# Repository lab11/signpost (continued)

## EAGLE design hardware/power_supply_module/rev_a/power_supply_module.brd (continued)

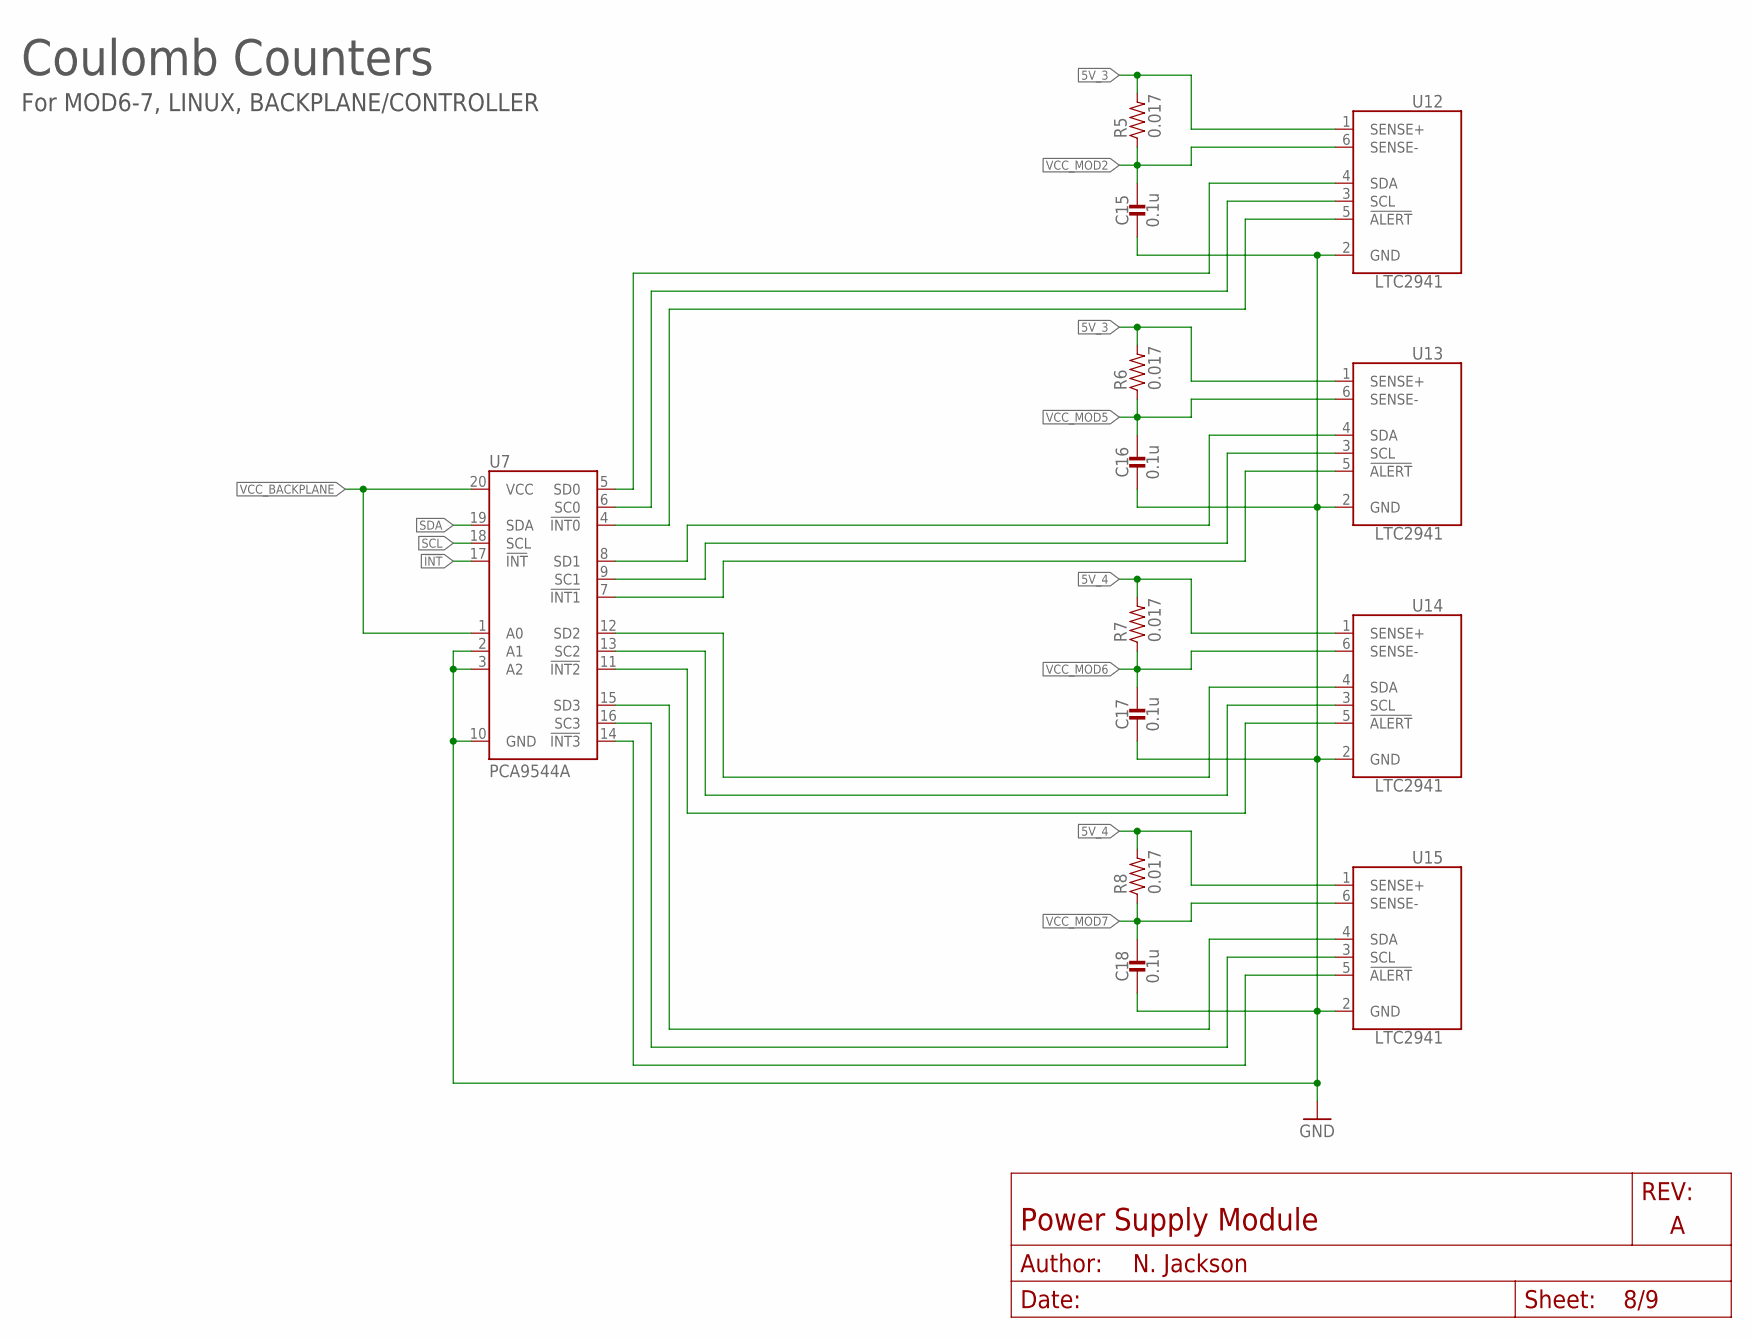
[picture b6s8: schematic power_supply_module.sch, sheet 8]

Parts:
C15, C16, C17, C18: 0.1u; 0402_CAP
R5, R6, R7, R8: 0.017; 0805_RES
U7: PCA9544A; SO20L
U12, U13, U14, U15: LTC2941; DFN-6-2MMX3MM

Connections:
5V_3: R5.2, R6.2, U12.1 (SENSE+), U13.1 (SENSE+); also elsewhere on the board
5V_4: R7.2, R8.2, U14.1 (SENSE+), U15.1 (SENSE+); also elsewhere on the board
!INT: U7.17 (!INT); also elsewhere on the board
GND: C15.2, C16.2, C17.2, C18.2, U7.2 (A1), U7.3 (A2), U7.10 (GND), U12.2 (GND), U13.2 (GND), U14.2 (GND), U15.2 (GND); also elsewhere on the board
unnamed: U7.5 (SD0), U12.4 (SDA)
unnamed: U7.6 (SC0), U12.3 (SCL)
unnamed: U7.12 (SD2), U14.4 (SDA)
unnamed: U7.13 (SC2), U14.3 (SCL)
unnamed: U7.11 (!INT2), U14.5 (!ALERT)
unnamed: U7.15 (SD3), U15.4 (SDA)
unnamed: U7.16 (SC3), U15.3 (SCL)
unnamed: U7.14 (!INT3), U15.5 (!ALERT)
unnamed: U7.4 (!INT0), U12.5 (!ALERT)
unnamed: U7.8 (SD1), U13.4 (SDA)
unnamed: U7.9 (SC1), U13.3 (SCL)
unnamed: U7.7 (!INT1), U13.5 (!ALERT)
SCL: U7.18 (SCL); also elsewhere on the board
SDA: U7.19 (SDA); also elsewhere on the board
VCC_BACKPLANE: U7.1 (A0), U7.20 (VCC); also elsewhere on the board
VCC_MOD2: C15.1, R5.1, U12.6 (SENSE-); also elsewhere on the board
VCC_MOD5: C16.1, R6.1, U13.6 (SENSE-); also elsewhere on the board
VCC_MOD6: C17.1, R7.1, U14.6 (SENSE-); also elsewhere on the board
VCC_MOD7: C18.1, R8.1, U15.6 (SENSE-); also elsewhere on the board

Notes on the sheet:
Coulomb Counters
For MOD6-7, LINUX, BACKPLANE/CONTROLLER

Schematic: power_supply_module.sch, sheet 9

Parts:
TP1, TP2, TP3, TP4, TP5, TP6, TP7, TP8, TP9, TP10, TP11, TP12, TP13, TP14, TP15, TP16, TP17, TP18, TP19, TP20: TEST_POINT_0.040IN; TESTPOINT_0.040IN

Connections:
3V3: TP5.TESTPOINT; also elsewhere on the board
5V_1: TP6.TESTPOINT; also elsewhere on the board
5V_2: TP7.TESTPOINT; also elsewhere on the board
5V_3: TP8.TESTPOINT; also elsewhere on the board
5V_4: TP9.TESTPOINT; also elsewhere on the board
!INT: TP20.TESTPOINT; also elsewhere on the board
GND: TP4.TESTPOINT; also elsewhere on the board
SCL: TP19.TESTPOINT; also elsewhere on the board
SDA: TP18.TESTPOINT; also elsewhere on the board
VBATT: TP3.TESTPOINT; also elsewhere on the board
VCC_BACKPLANE: TP11.TESTPOINT; also elsewhere on the board
VCC_LINUX: TP10.TESTPOINT; also elsewhere on the board
VCC_MOD0: TP12.TESTPOINT; also elsewhere on the board
VCC_MOD1: TP13.TESTPOINT; also elsewhere on the board
VCC_MOD2: TP14.TESTPOINT; also elsewhere on the board
VCC_MOD5: TP15.TESTPOINT; also elsewhere on the board
VCC_MOD6: TP16.TESTPOINT; also elsewhere on the board
VCC_MOD7: TP17.TESTPOINT; also elsewhere on the board
VSOL+: TP1.TESTPOINT; also elsewhere on the board
VSOL-: TP2.TESTPOINT; also elsewhere on the board

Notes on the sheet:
Debugging

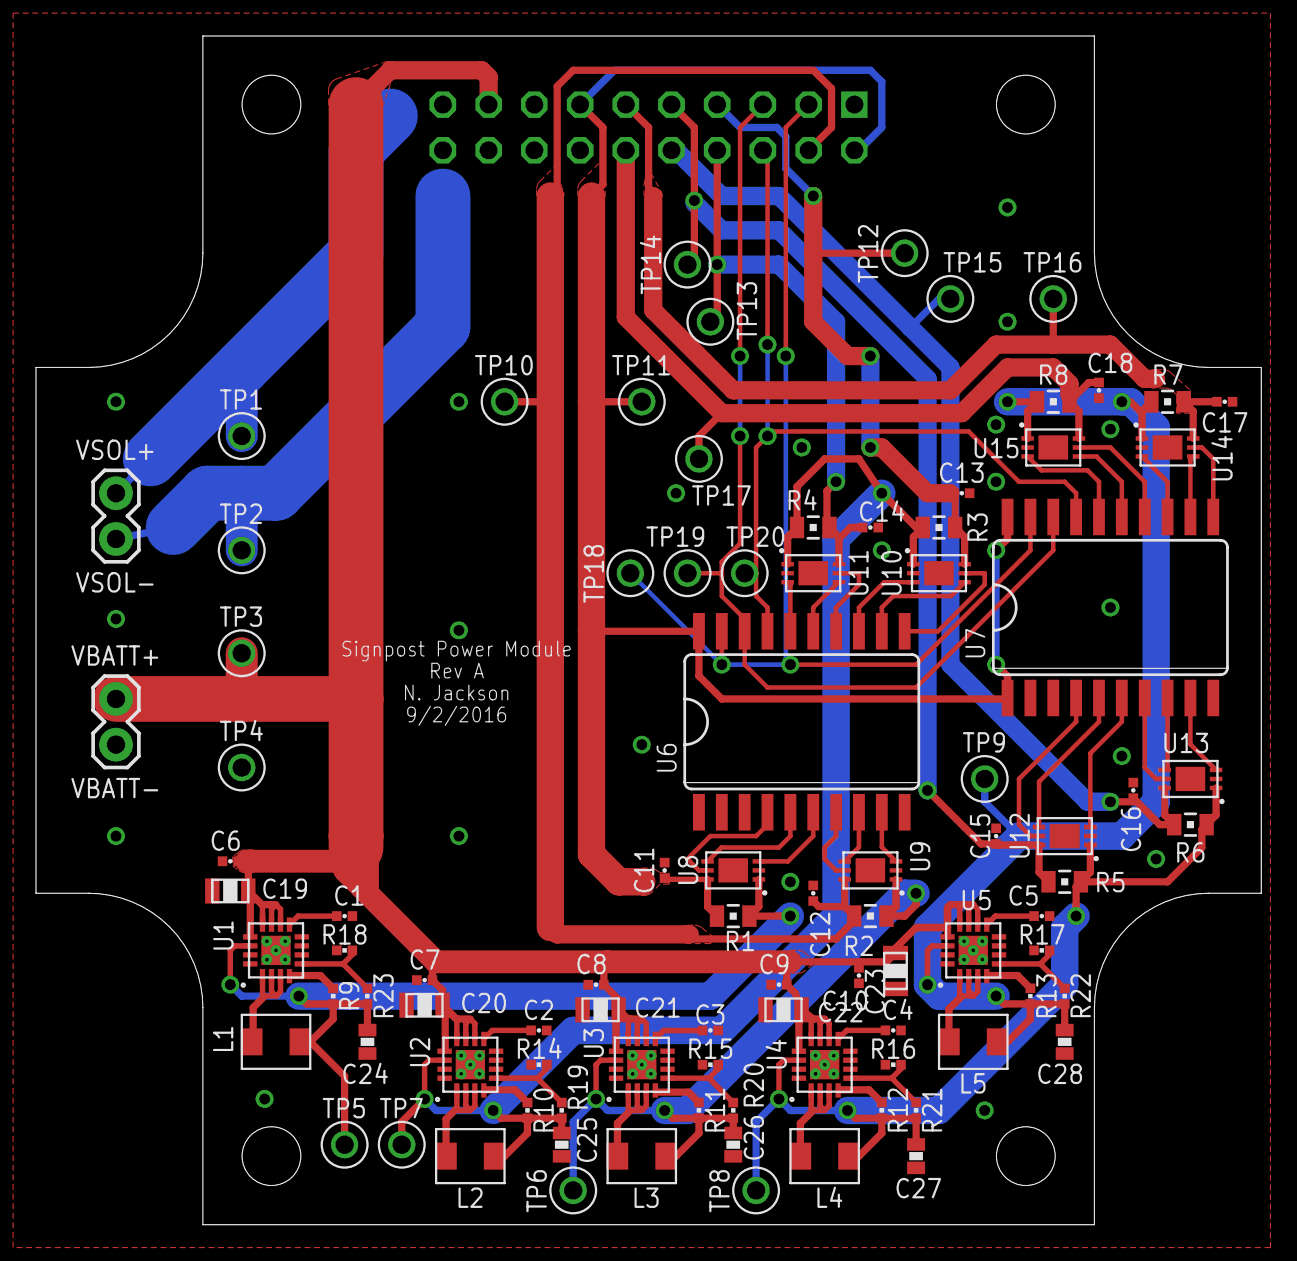
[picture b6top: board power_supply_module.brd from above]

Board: 2 copper layers, 68.1 x 66.0 mm, 95 parts (0 on the bottom side), 64 nets.

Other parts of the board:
U$1: UCB_CAL_350MIL
